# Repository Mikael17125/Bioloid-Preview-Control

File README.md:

# Project Documentation

For detailed information and instructions, please refer to the comprehensive documentation available on [Notion](https://www.notion.so/mikaelnias/Bioloid-Preview-Control-c7b654bd0ebc4cd78e7dc0772060c5e5).

## Simulation Preview

Explore the simulation of Bioloid Preview Control by visiting the [simulation page](https://www.notion.so/mikaelnias/Bioloid-Preview-Control-c7b654bd0ebc4cd78e7dc0772060c5e5).

## Real World Video Documentation
Watch the real-world implementation in action on YouTube: [Bioloid Preview Control](https://www.youtube.com/watch?v=nTc8X4GceEk&feature=youtu.be).

## Interface Display

Visualize the user interface designed for Bioloid Preview Control.

## Author
- Mikael Nias

Feel free to reach out if you have any questions or need further assistance.

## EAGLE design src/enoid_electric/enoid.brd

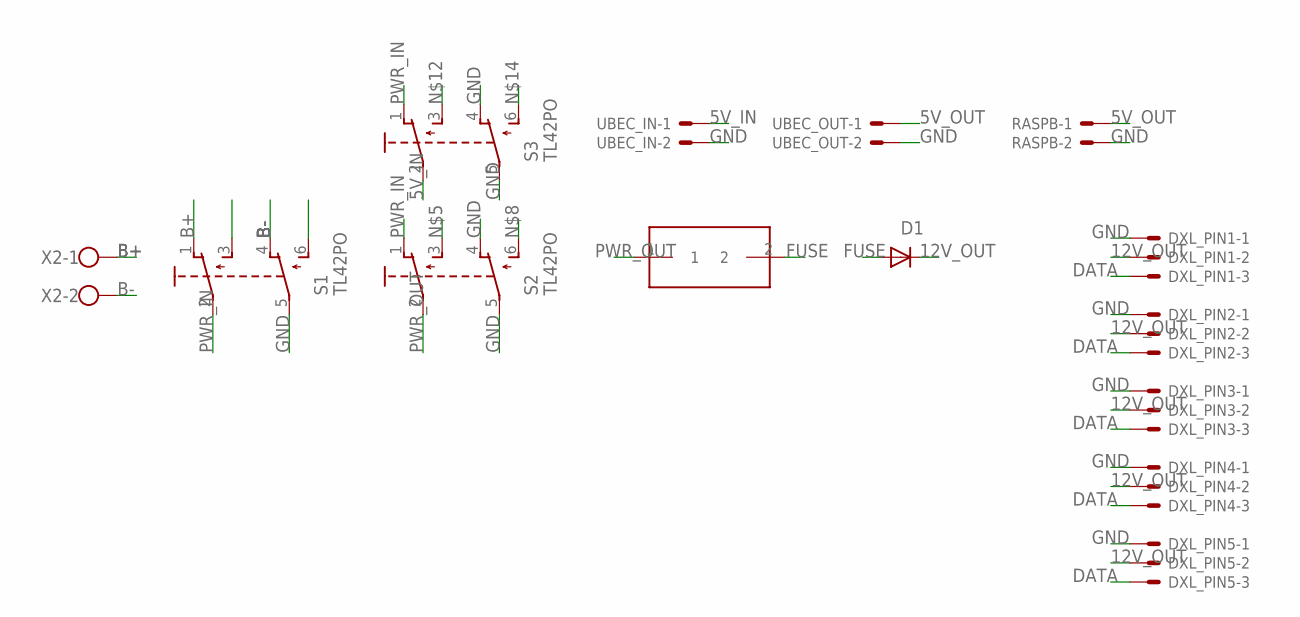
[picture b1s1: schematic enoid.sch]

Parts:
D1: BY500; DO201-15
DXL_PIN1, DXL_PIN2, DXL_PIN3, DXL_PIN4, DXL_PIN5: 22-23-2031
FUSE: FUSE-30X8; FUSE
RASPB: 22-23-2021
S1, S2, S3: TL42PO; TL4XPO
UBEC_IN: 22-23-2021
UBEC_OUT: 22-23-2021
X2: W237-102

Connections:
5V_IN: S3.2, UBEC_IN.1
5V_OUT: RASPB.1, UBEC_OUT.1
12V_OUT: D1.C, DXL_PIN1.2, DXL_PIN2.2, DXL_PIN3.2, DXL_PIN4.2, DXL_PIN5.2
B+: S1.1 (O), X2.1
B-: S1.4 (O1), X2.2
DATA: DXL_PIN1.3, DXL_PIN2.3, DXL_PIN3.3, DXL_PIN4.3, DXL_PIN5.3
FUSE: D1.A, FUSE.2
GND: DXL_PIN1.1, DXL_PIN2.1, DXL_PIN3.1, DXL_PIN4.1, DXL_PIN5.1, RASPB.2, S1.5 (P1), S2.4 (O1), S2.5 (P1), S3.4 (O1), S3.5 (P1), UBEC_IN.2, UBEC_OUT.2
PWR_IN: S1.2, S2.1 (O), S3.1 (O)
PWR_OUT: FUSE.1, S2.2

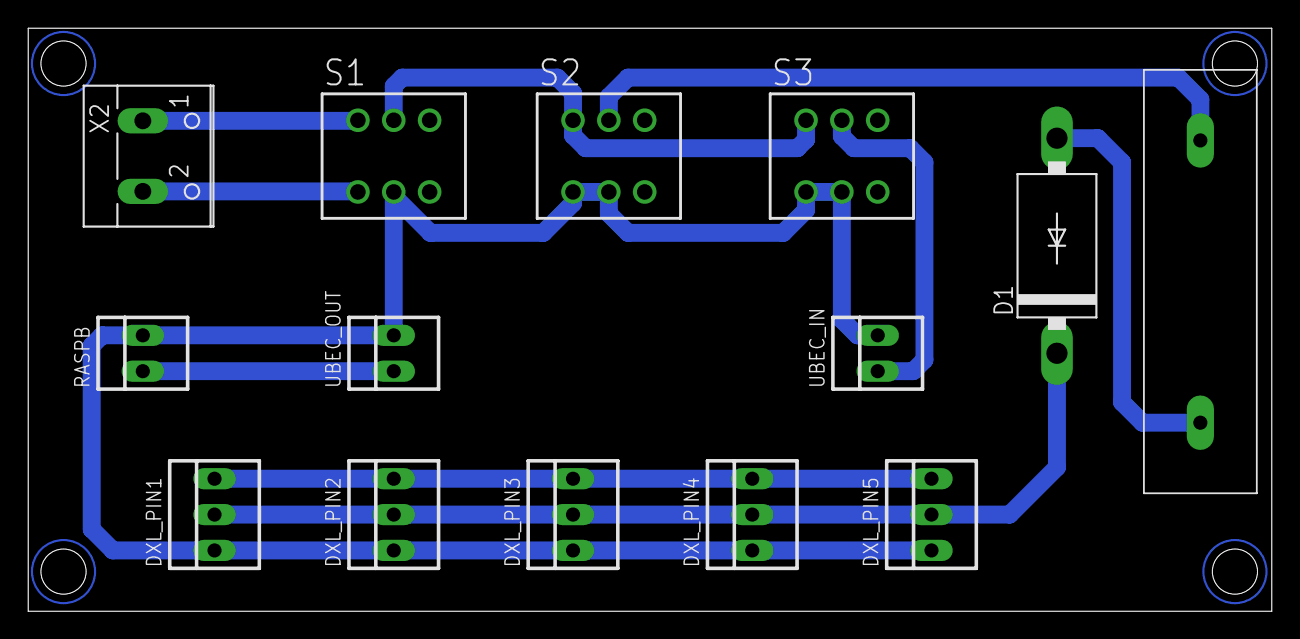
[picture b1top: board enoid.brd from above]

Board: 2 copper layers, 88.1 x 41.3 mm, 14 parts (0 on the bottom side), 10 nets.

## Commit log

2021-09-29 mpu opengl
2021-10-09 simulator
2021-10-09 refactor
2021-10-14 IK for one leg
2021-11-02 electric schematic
2022-01-20 Walk Node
2022-01-31 rosweb-interface
2022-02-27 add record feature
2022-03-15 add git ignore
2022-03-15 update gitignore
2022-03-15 push test
2022-03-22 update git ignore
2022-03-22 3-22-2022
2022-03-22 tes init git
2022-03-22 update code 22 Maret 2022
2022-06-28 Add example docker
2023-11-08 add asset folder
2023-11-08 Add new file
2024-04-15 Create LICENSE
